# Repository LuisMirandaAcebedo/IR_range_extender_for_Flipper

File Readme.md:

# IR Range Extender for Flipper Zero

Flipper Zero has de ability of sending IR signals, but it has very short range.
This boards allows you to extend the range of your Flipper Zero using IR.

The difference with other boards is that this one has both wide angle (120º) group of high power IR emitters and narrow angle (14º) group of high power IR emitters, so you can reach undefined targets (when you don't know where exactly is the IR receiver) and far and well defined targets.

These groups of IR LEDs are selectable by a tiny switch.

The board connects to Flipper in a way that barely increases the size of the device.

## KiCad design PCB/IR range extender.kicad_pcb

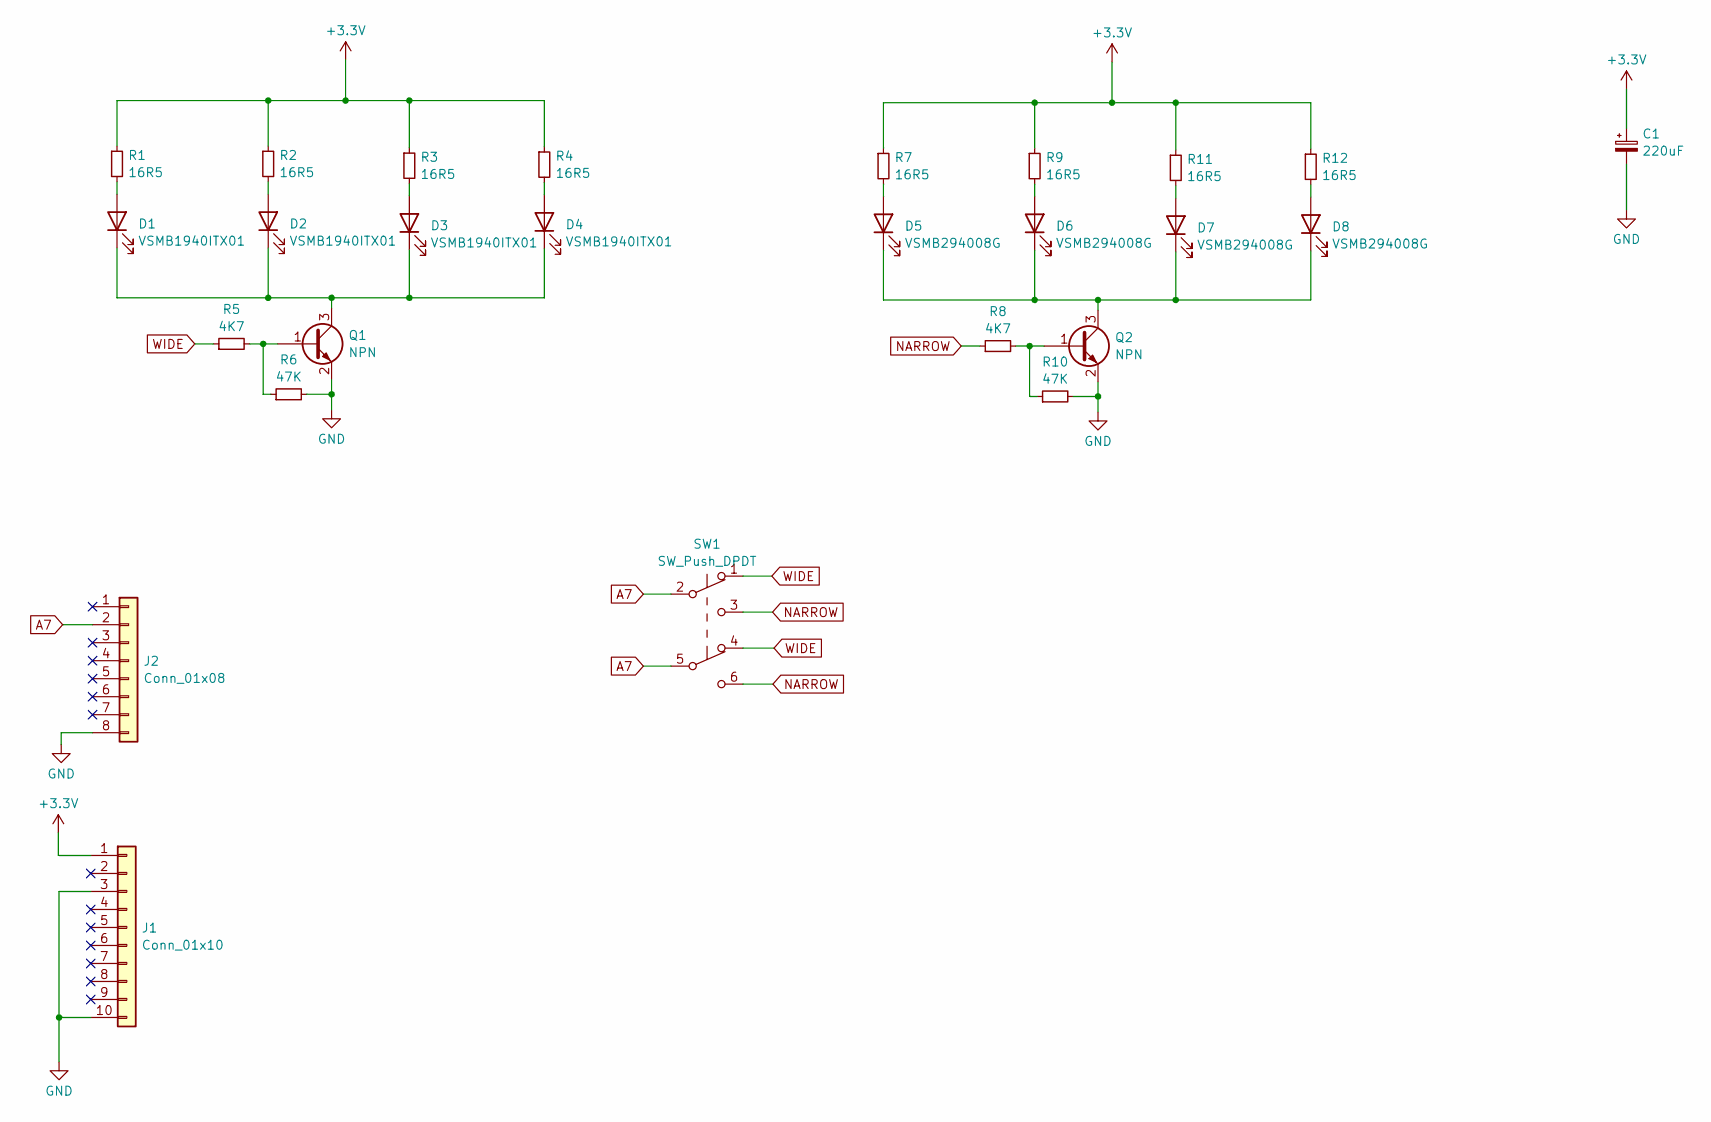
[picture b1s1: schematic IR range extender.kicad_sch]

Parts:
C1: 220uF; CP_EIA-7343-15_Kemet-W; Digi-Key_PN 718-293D227X06R3D2TE3CT-ND
D1, D2, D3, D4: VSMB1940ITX01; DIO_VSMB1940ITX01; Digi-Key_PN VSMB1940ITX01CT-ND
D5, D6, D7, D8: VSMB294008G; DIO_VSMB294008G; Digi-Key_PN VSMB294008GCT-ND
J1: Conn_01x10; PinHeader_1x10_P2.54mm_Vertical
J2: Conn_01x08; PinHeader_1x08_P2.54mm_Vertical
Q1, Q2: NPN; SOT-23-3; Digi-Key_PN NSS40201LT1GOSCT-ND
R1, R2, R3, R4, R7, R9, R11, R12: 16R5; R_0805_2012Metric; Digi-Key_PN 10-ERJ-P06F16R0VCT-ND
R5, R8: 4K7; R_0603_1608Metric; Digi-Key_PN 311-4.70KHRCT-ND
R6, R10: 47K; R_0603_1608Metric; Digi-Key_PN 311-47.0KHRCT-ND
SW1: SW_Push_DPDT; JS202011JAQN_CNK; Digi-Key_PN CKN10722CT-ND

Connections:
+3.3V: C1.1, J1.1, R1.1, R2.1, R3.1, R4.1, R7.1, R9.1, R11.1, R12.1
A7: J2.2, SW1.2 (B), SW1.5 (B)
GND: C1.2, J1.3, J1.10, J2.8, Q1.2 (E), Q2.2 (E), R6.2, R10.2
NARROW: R8.1, SW1.3 (C), SW1.6 (C)
unnamed: D1.2 (A), R1.2
unnamed: D1.1 (K), D2.1 (K), D3.1 (K), D4.1 (K), Q1.3 (C)
unnamed: D2.2 (A), R2.2
unnamed: D3.2 (A), R3.2
unnamed: D4.2 (A), R4.2
unnamed: D5.2 (A), R7.2
unnamed: D5.1 (K), D6.1 (K), D7.1 (K), D8.1 (K), Q2.3 (C)
unnamed: D6.2 (A), R9.2
unnamed: D7.2 (A), R11.2
unnamed: D8.2 (A), R12.2
unnamed: Q1.1 (B), R5.2, R6.1
unnamed: Q2.1 (B), R8.2, R10.1
WIDE: R5.1, SW1.1 (A), SW1.4 (A)

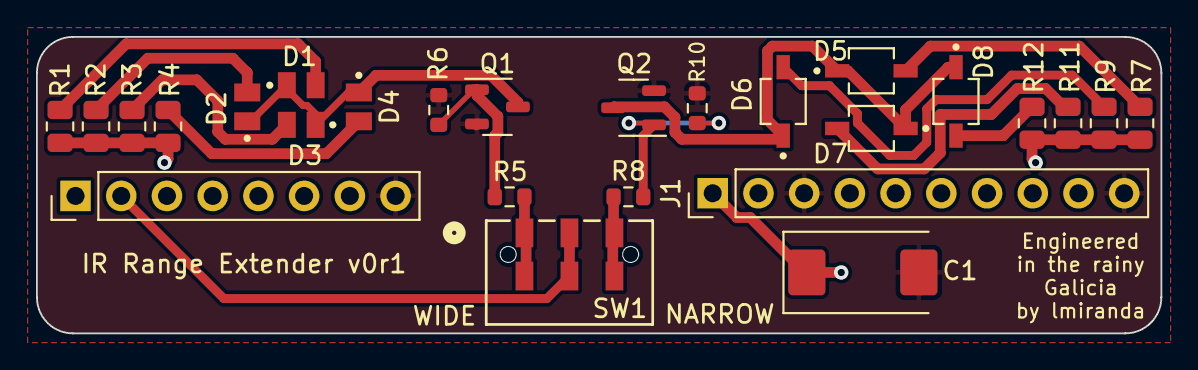
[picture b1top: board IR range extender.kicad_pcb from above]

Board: 4 copper layers, 62.5 x 16.5 mm, 26 parts (0 on the bottom side), 17 nets.

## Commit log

2024-01-16 Add files
